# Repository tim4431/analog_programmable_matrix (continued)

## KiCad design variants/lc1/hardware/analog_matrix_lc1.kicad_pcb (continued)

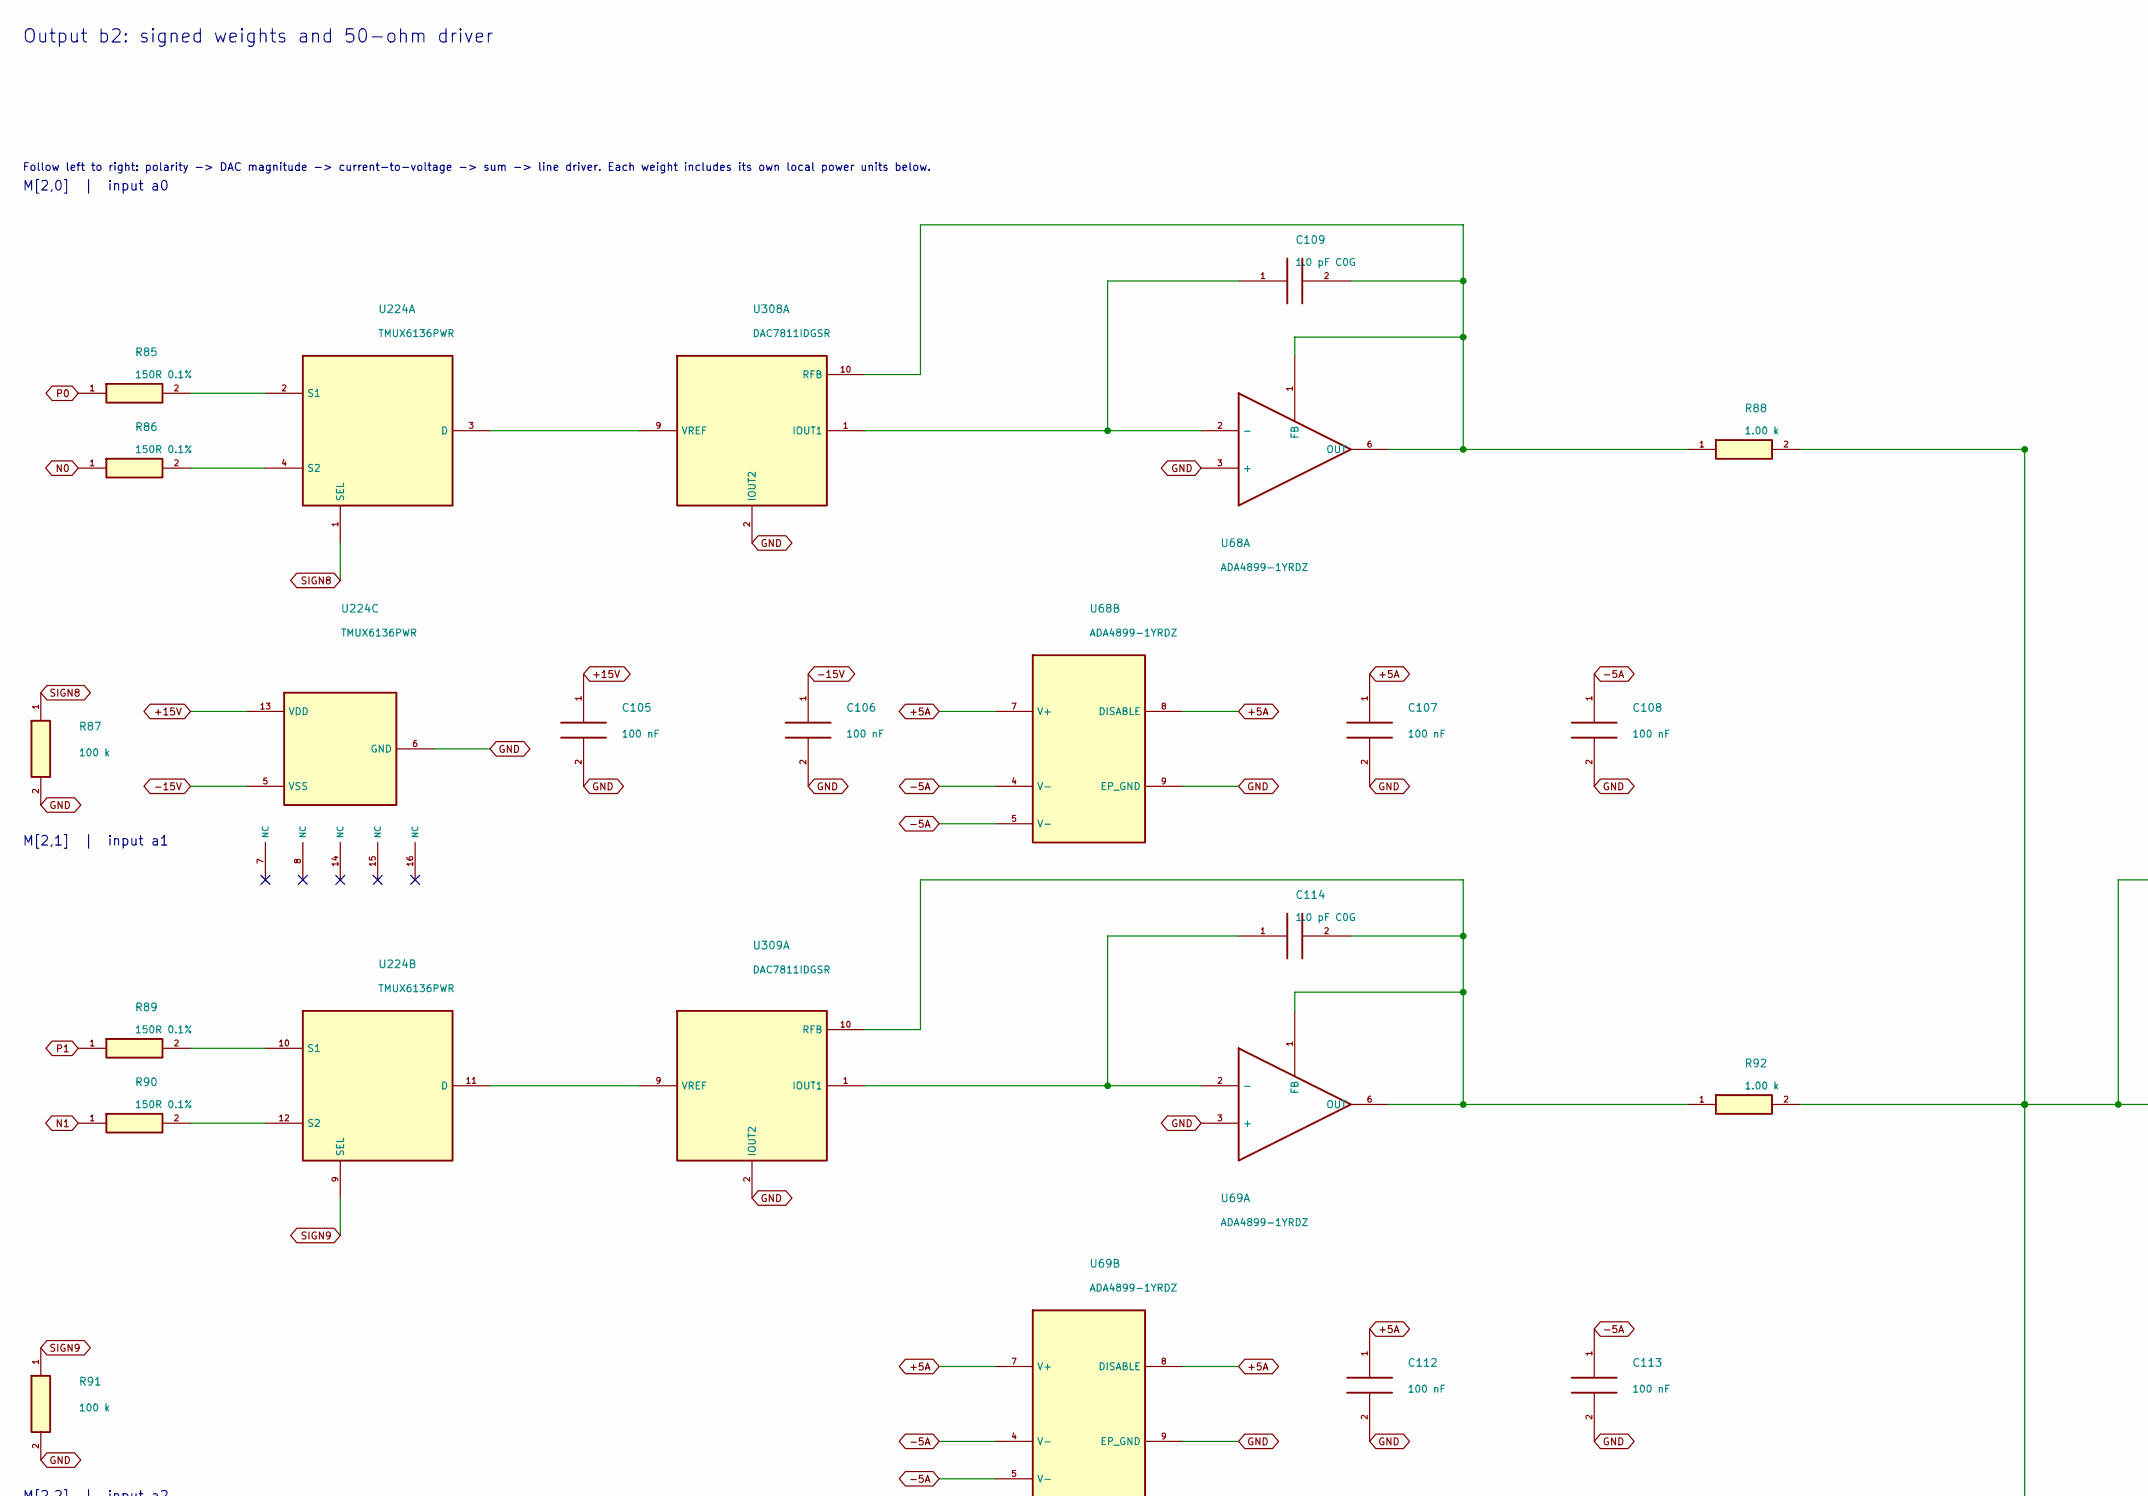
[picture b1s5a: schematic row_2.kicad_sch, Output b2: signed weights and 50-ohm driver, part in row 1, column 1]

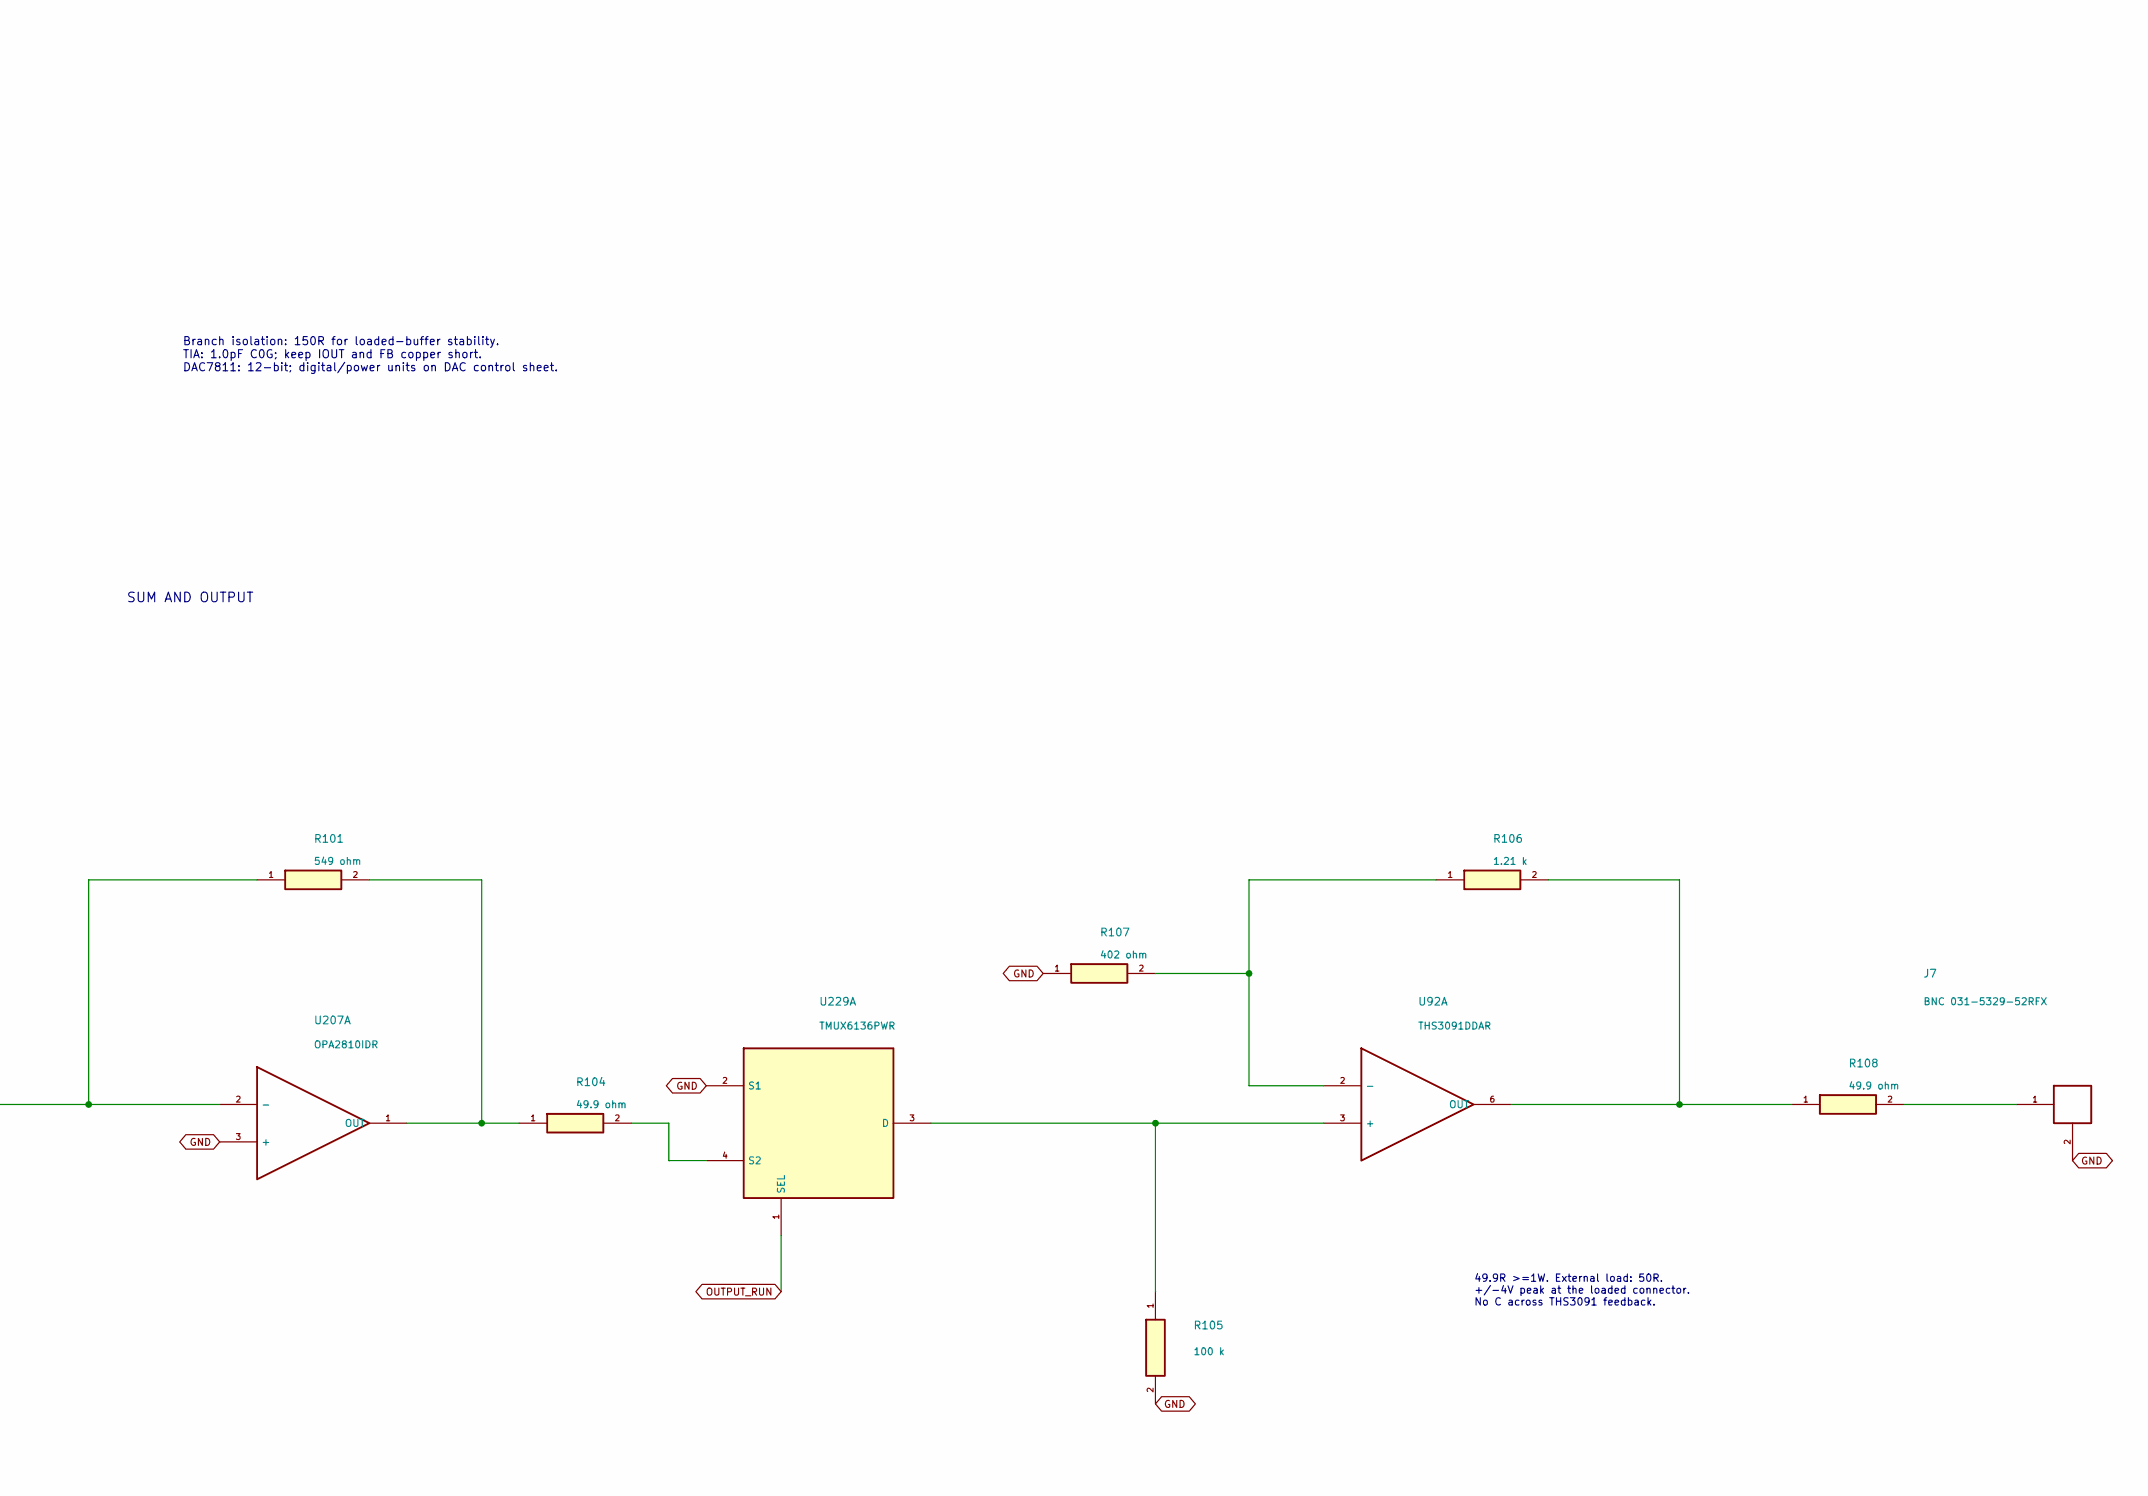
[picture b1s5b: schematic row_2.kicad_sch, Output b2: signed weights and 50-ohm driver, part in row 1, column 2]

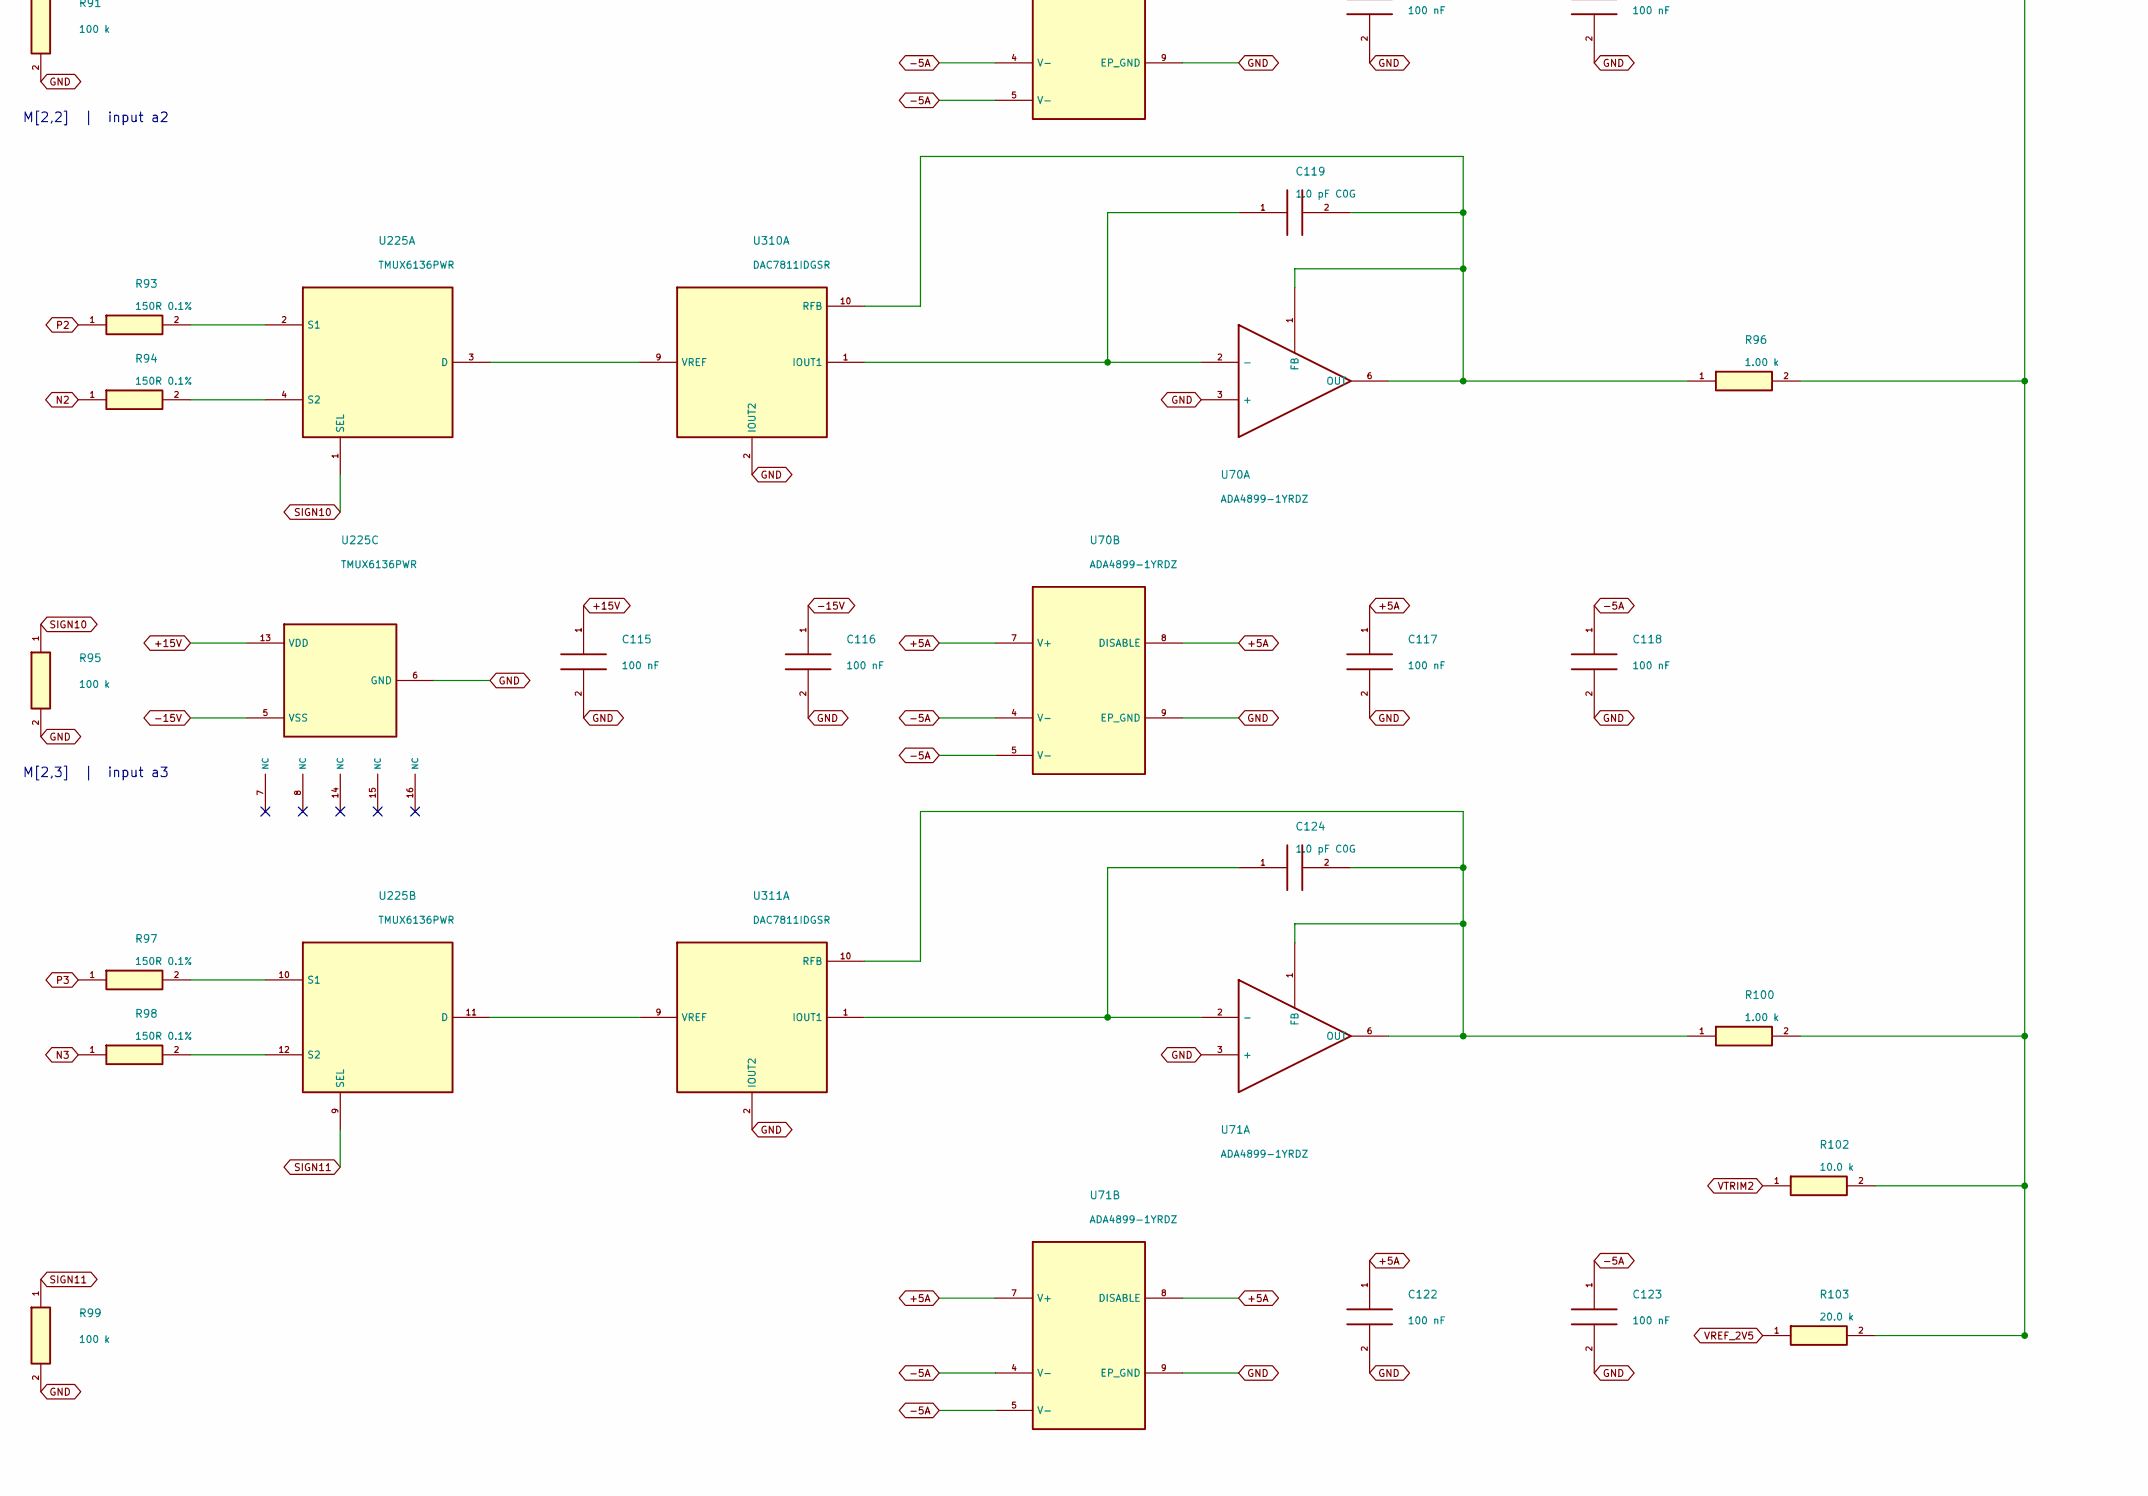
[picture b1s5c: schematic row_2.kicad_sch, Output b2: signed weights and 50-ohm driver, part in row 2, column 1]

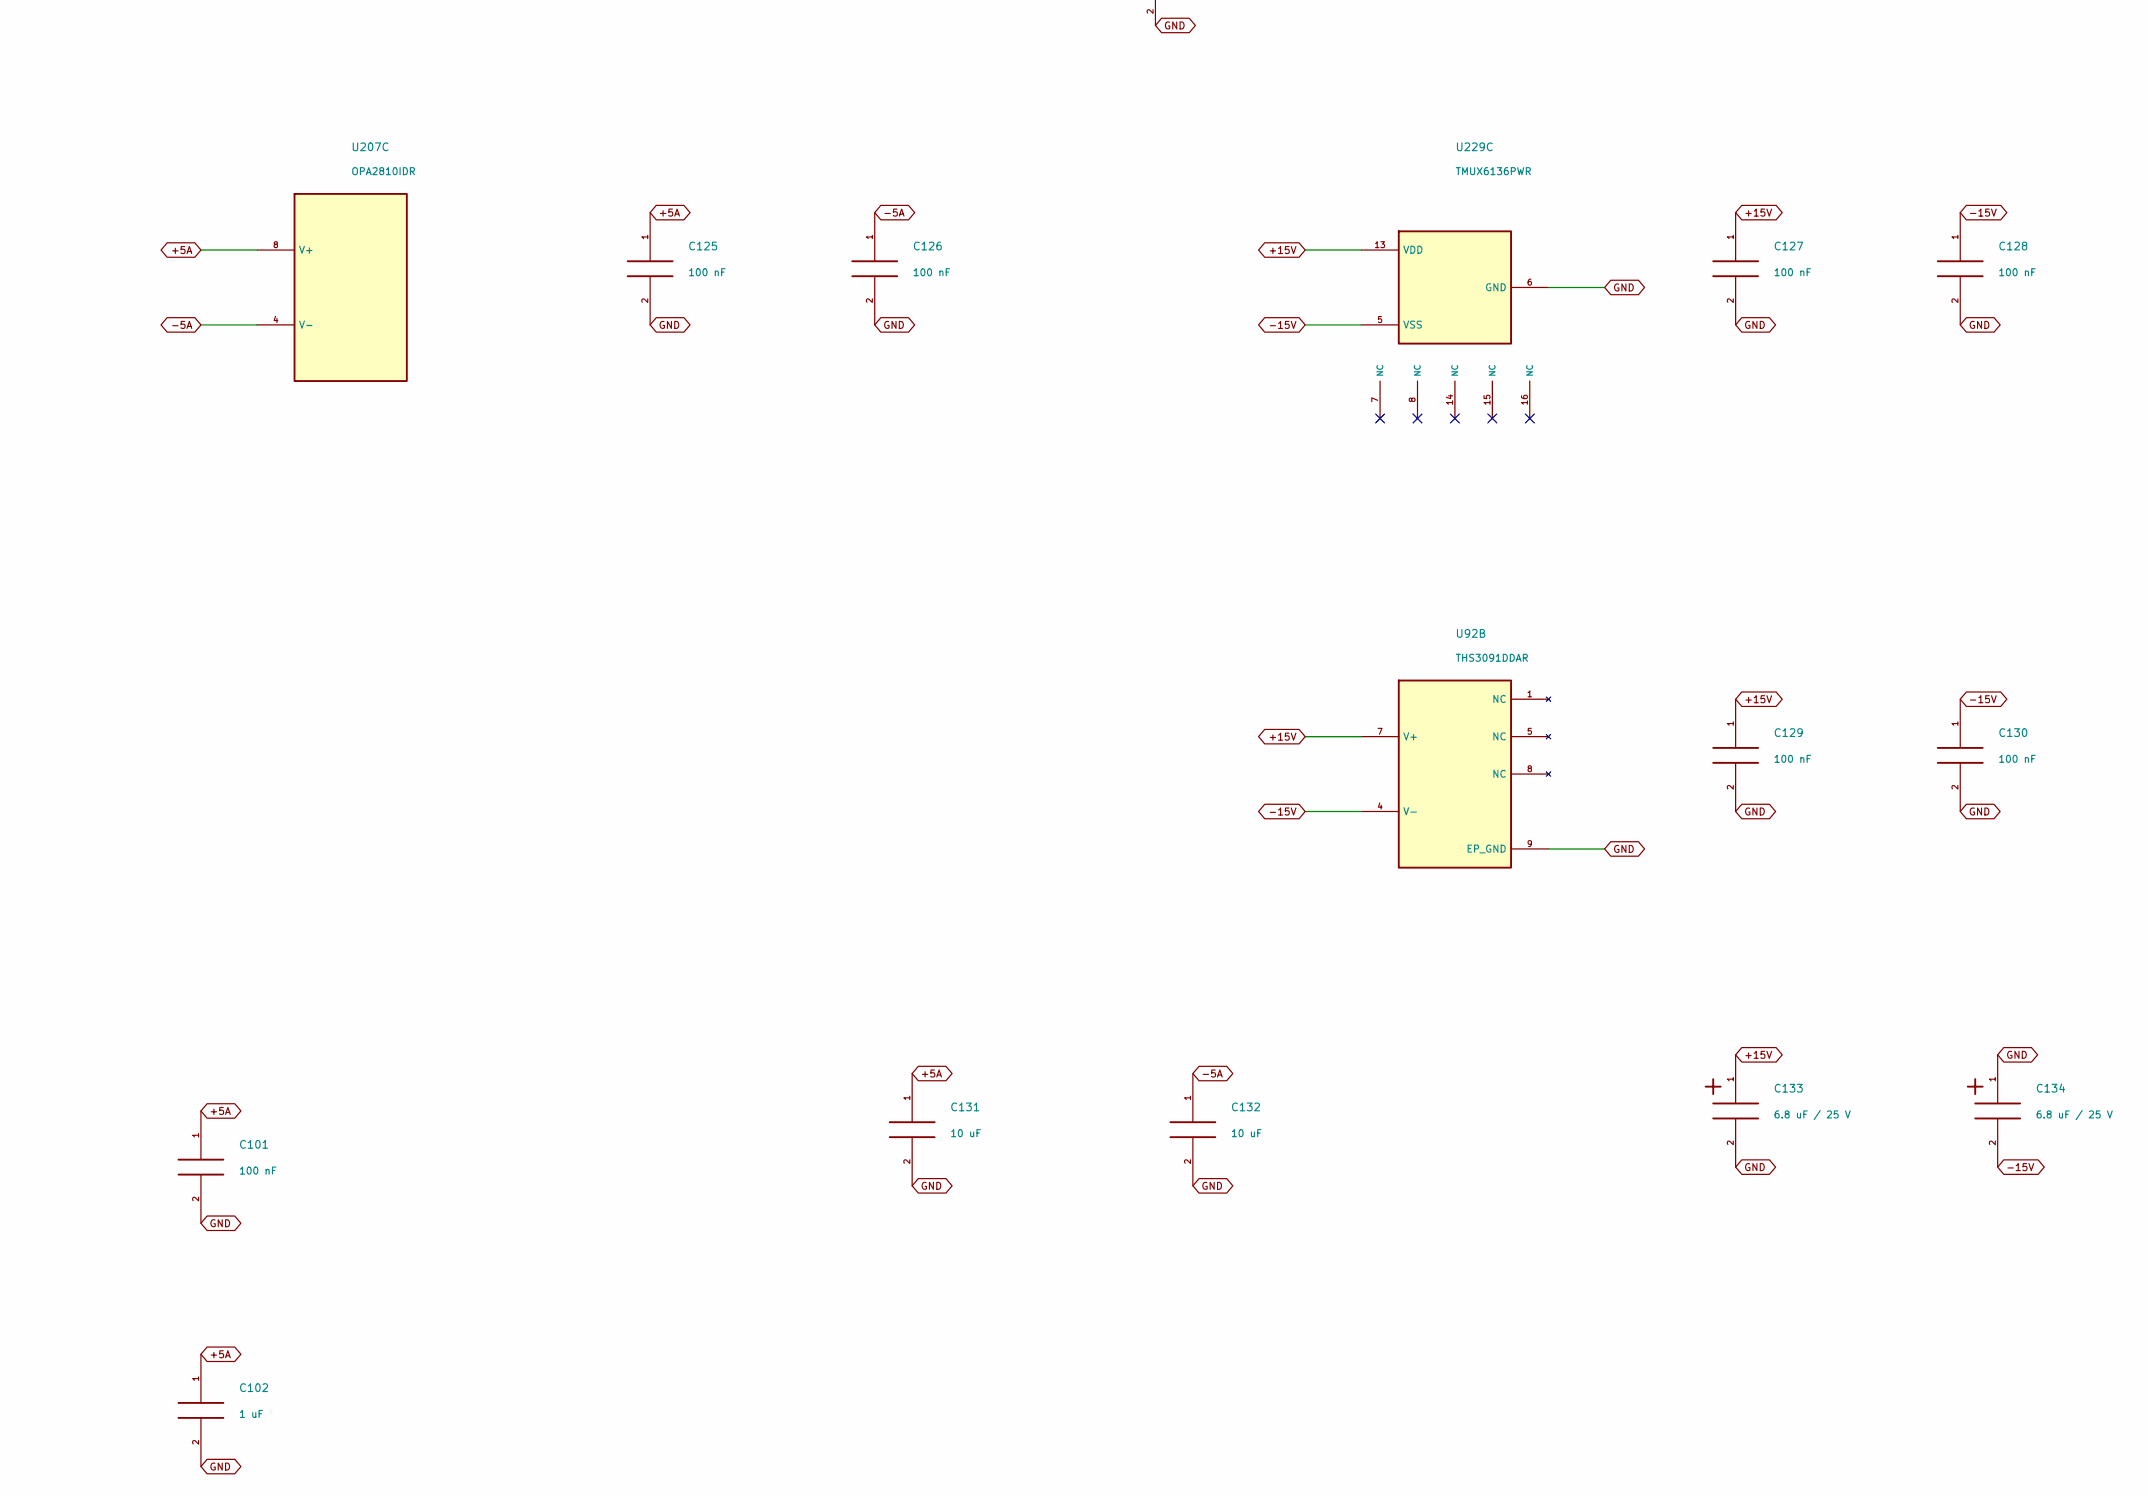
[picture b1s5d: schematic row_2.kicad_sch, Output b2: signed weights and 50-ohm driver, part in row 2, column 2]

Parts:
C101, C105, C106, C107, C108, C112, C113, C115, C116, C117, C118, C122, C123, C125, C126, C127, C128, C129, C130: 100 nF; C_0603_1608Metric; Rating 25V X7R minimum; effective C after bias
C102: 1 uF; C_0805_2012Metric; Rating 25V X7R minimum; effective C after bias
C109, C114, C119, C124: 1.0 pF C0G; C_0402_1005Metric; Rating 50V C0G, +/-0.1pF; stray capacitance in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
C131, C132: 10 uF; C_0805_2012Metric; Rating 25V X7R minimum; effective C after bias
C133, C134: 6.8 uF / 25 V; CP_EIA-3216-18_Kemet-A; Rating 25V polarized
J7: BNC 031-5329-52RFX; BNC_Amphenol_031-5329-52RFX_Vertical
R85, R86, R89, R90, R93, R94, R97, R98: 150R 0.1%; R_0603_1608Metric; Rating 0.1%, <=25ppm/C; 0.1W minimum
R87, R91, R95, R99, R105: 100 k; R_0603_1608Metric; Rating 0.1%, <=25ppm/C; 0.1W minimum
R88, R92, R96, R100: 1.00 k; R_0603_1608Metric; Rating 0.1%, <=25ppm/C; 0.1W minimum
R101: 549 ohm; R_0603_1608Metric; Rating 0.1%, <=25ppm/C; 0.1W minimum
R102: 10.0 k; R_0603_1608Metric; Rating 0.1%, <=25ppm/C; 0.1W minimum
R103: 20.0 k; R_0603_1608Metric; Rating 0.1%, <=25ppm/C; 0.1W minimum
R104: 49.9 ohm; R_0603_1608Metric; Rating 0.1%, <=25ppm/C; 0.1W minimum
R106: 1.21 k; R_0603_1608Metric; Rating 0.1%, <=25ppm/C; 0.1W minimum
R107: 402 ohm; R_0603_1608Metric; Rating 0.1%, <=25ppm/C; 0.1W minimum
R108: 49.9 ohm; R_2512_6332Metric; Rating 0.1%, <=25ppm/C; >=1W
U68, U69, U70, U71: ADA4899-1YRDZ; ADA4899_RD8_EP2.29x2.29
U92: THS3091DDAR; SOIC-8-1EP_3.9x4.9mm_P1.27mm_EP2.95x4.9mm_Mask2.71x3.4mm_Th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
U207: OPA2810IDR; SOIC-8_3.9x4.9mm_P1.27mm
U224, U225, U229: TMUX6136PWR; TSSOP-16_4.4x5mm_P0.65mm
U308, U309, U310, U311: DAC7811IDGSR; VSSOP-10_3x3mm_P0.5mm

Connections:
+5A: C101.1, C102.1, C107.1, C112.1, C117.1, C122.1, C125.1, C131.1, U68.7 (V+), U68.8 (DISABLE), U69.7 (V+), U69.8 (DISABLE), U70.7 (V+), U70.8 (DISABLE), U71.7 (V+), U71.8 (DISABLE), U207.8 (V+); also elsewhere on the board
+15V: C105.1, C115.1, C127.1, C129.1, C133.1, U92.7 (V+), U224.13 (VDD), U225.13 (VDD), U229.13 (VDD); also elsewhere on the board
-5A: C108.1, C113.1, C118.1, C123.1, C126.1, C132.1, U68.4 (V-), U68.5 (V-), U69.4 (V-), U69.5 (V-), U70.4 (V-), U70.5 (V-), U71.4 (V-), U71.5 (V-), U207.4 (V-); also elsewhere on the board
-15V: C106.1, C116.1, C128.1, C130.1, C134.2, U92.4 (V-), U224.5 (VSS), U225.5 (VSS), U229.5 (VSS); also elsewhere on the board
GND: C101.2, C102.2, C105.2, C106.2, C107.2, C108.2, C112.2, C113.2, C115.2, C116.2, C117.2, C118.2, C122.2, C123.2, C125.2, C126.2, C127.2, C128.2, C129.2, C130.2, C131.2, C132.2, C133.2, C134.1, J7.2, R87.2, R91.2, R95.2, R99.2, R105.2, R107.1, U68.3 (+), U68.9 (EP_GND), U69.3 (+), U69.9 (EP_GND), U70.3 (+), U70.9 (EP_GND), U71.3 (+), U71.9 (EP_GND), U92.9 (EP_GND), U207.3 (+), U224.6 (GND), U225.6 (GND), U229.2 (S1), U229.6 (GND), U308.2 (IOUT2), U309.2 (IOUT2), U310.2 (IOUT2), U311.2 (IOUT2); also elsewhere on the board
N0: R86.1; also elsewhere on the board
N1: R90.1; also elsewhere on the board
N2: R94.1; also elsewhere on the board
N3: R98.1; also elsewhere on the board
unnamed: J7.1, R108.2
unnamed: R106.1, R107.2, U92.2 (-)
unnamed: R106.2, R108.1, U92.6 (OUT)
unnamed: R88.2, R92.2, R96.2, R100.2, R101.1, R102.2, R103.2, U207.2 (-)
unnamed: R101.2, R104.1, U207.1 (OUT)
unnamed: U224.3 (D), U308.9 (VREF)
unnamed: R85.2, U224.2 (S1)
unnamed: R86.2, U224.4 (S2)
unnamed: U224.11 (D), U309.9 (VREF)
unnamed: R89.2, U224.10 (S1)
unnamed: R90.2, U224.12 (S2)
unnamed: U225.3 (D), U310.9 (VREF)
unnamed: R93.2, U225.2 (S1)
unnamed: R94.2, U225.4 (S2)
unnamed: U225.11 (D), U311.9 (VREF)
unnamed: R97.2, U225.10 (S1)
unnamed: R98.2, U225.12 (S2)
unnamed: R105.1, U92.3 (+), U229.3 (D)
unnamed: R104.2, U229.4 (S2)
unnamed: C109.1, U68.2 (-), U308.1 (IOUT1)
unnamed: C109.2, R88.1, U68.1 (FB), U68.6 (OUT), U308.10 (RFB)
unnamed: C114.1, U69.2 (-), U309.1 (IOUT1)
unnamed: C114.2, R92.1, U69.1 (FB), U69.6 (OUT), U309.10 (RFB)
unnamed: C119.1, U70.2 (-), U310.1 (IOUT1)
unnamed: C119.2, R96.1, U70.1 (FB), U70.6 (OUT), U310.10 (RFB)
unnamed: C124.1, U71.2 (-), U311.1 (IOUT1)
unnamed: C124.2, R100.1, U71.1 (FB), U71.6 (OUT), U311.10 (RFB)
OUTPUT_RUN: U229.1 (SEL); also elsewhere on the board
P0: R85.1; also elsewhere on the board
P1: R89.1; also elsewhere on the board
P2: R93.1; also elsewhere on the board
P3: R97.1; also elsewhere on the board
SIGN8: R87.1, U224.1 (SEL); also elsewhere on the board
SIGN9: R91.1, U224.9 (SEL); also elsewhere on the board
SIGN10: R95.1, U225.1 (SEL); also elsewhere on the board
SIGN11: R99.1, U225.9 (SEL); also elsewhere on the board
VREF_2V5: R103.1; also elsewhere on the board
VTRIM2: R102.1; also elsewhere on the board

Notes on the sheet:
Output b2: signed weights and 50-ohm driver
Follow left to right: polarity -> DAC magnitude -> current-to-voltage -> sum -> line driver. Each weight includes its own local power units below.
M[2,0] | input a0
M[2,1] | input a1
M[2,2] | input a2
M[2,3] | input a3
SUM AND OUTPUT
49.9R >=1W. External load: 50R. +/-4V peak at the loaded connector. No C across THS3091 feedback.
Branch isolation: 150R for loaded-buffer stability. TIA: 1.0pF C0G; keep IOUT and FB copper short. DAC7811: 12-bit; digital/power units on DAC control sheet.
